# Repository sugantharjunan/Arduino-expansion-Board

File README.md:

# Arduino UNO Sensor Shield PCB

An **Arduino UNO Compatible Sensor Shield** designed using **KiCad 10**. This PCB expands the Arduino UNO by providing dedicated Digital, Analog, Power, and Ground headers while integrating useful onboard components such as a buzzer, potentiometer, LEDs, and push buttons for rapid prototyping and embedded system development.

---

# Features

- Arduino UNO Compatible
- Digital I/O Expansion Headers
- Analog Input Headers
- Dedicated 5V & GND Headers
- On-board Buzzer
- 10K Potentiometer
- Power Indicator LED
- Two User LEDs
- Two Push Buttons
- Easy Sensor Connections
- Compact 2-Layer PCB
- Designed in KiCad 10

---

# Hardware Components

| Component | Quantity |
|-----------|---------:|
| Female Header 2.54mm | Multiple |
| Piezo Buzzer | 1 |
| 10K Potentiometer | 1 |
| Push Button | 2 |
| LEDs | 3 |
| 220Ω Resistors | 3 |
| Arduino UNO Header Set | 1 |

---

# PCB Specifications

| Parameter | Value |
|-----------|-------|
| PCB Software | KiCad 10 |
| PCB Layers | 2 |
| Board Type | Arduino UNO Shield |
| Header Pitch | 2.54 mm |
| Mounting Holes | 4 |
| PCB Color | Green |

---

# Pin Configuration

## Digital Pins

- D0 – D13
- PWM Support
- Dedicated 5V Header
- Dedicated GND Header

## Analog Pins

- A0 – A5

---

# Onboard Components

## 🔔 Buzzer

Provides audible feedback for alarms, notifications, and debugging.

---

## 🎛 Potentiometer

- 5V
- GND
- Analog Output

Useful for testing analog inputs and ADC applications.

---

## 💡 Power LED

Indicates that the board is powered.

---

## 💡 User LEDs

- LED connected to D2
- LED connected to D3

Useful for testing digital outputs.

---

## 🔘 Push Buttons

Two onboard push buttons connected for digital input testing.

---

# Applications

- Arduino Learning
- Sensor Interfacing
- Embedded System Development
- IoT Prototyping
- Robotics
- College Mini Projects
- Rapid Hardware Testing

---

# Folder Structure

```
Arduino-UNO-Sensor-Shield/
│
├── PCB/
│   ├── Arduino_UNO_Shield.kicad_pcb
│   ├── Arduino_UNO_Shield.kicad_sch
│
├── Gerber/
│
├── BOM/
│
├── Images/
│   ├── Top_3D.png
│   ├── Bottom_3D.png
│   ├── PCB_Layout.png
│   └── Schematic.png
│
├── README.md
│
└── LICENSE
```

---

# Software Used

- KiCad 10
- Git
- GitHub

---

# Future Improvements

- I2C Connector
- SPI Header
- Servo Headers
- OLED Interface
- Relay Output
- ESP32 Compatibility
- External Power Connector

---

# Author

**Suganth Arjunan**

📧 Email: your-email@example.com

🔗 GitHub: https://github.com/SuganthArjunan

💼 LinkedIn: https://www.linkedin.com/in/suganth-arjunan

🌐 Portfolio: https://sugantharjunan.github.io/SuganthArjunan-portfolio/

---

# License

This project is licensed under the MIT License.

---

⭐ **If you found this project useful, please give it a Star on GitHub!**

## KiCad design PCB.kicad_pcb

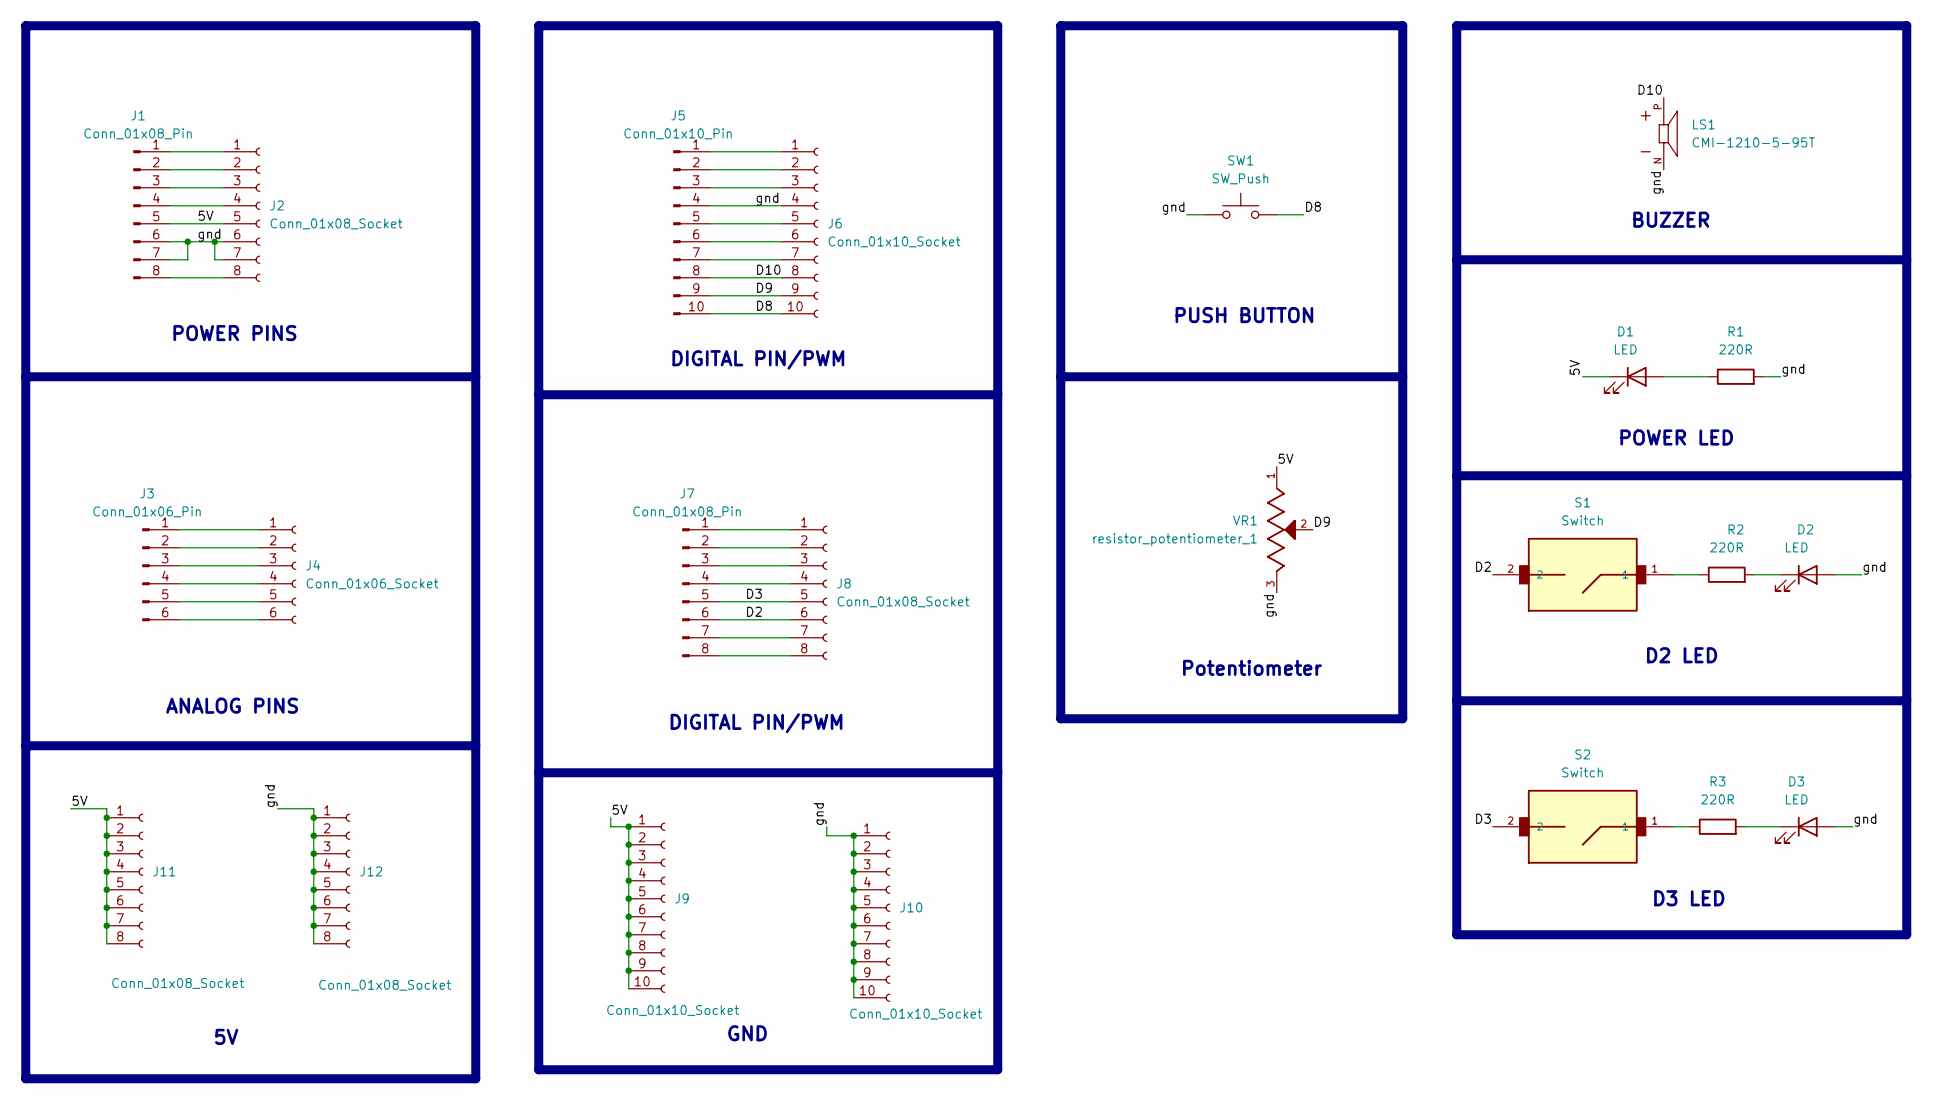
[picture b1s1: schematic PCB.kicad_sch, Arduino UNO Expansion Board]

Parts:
D1, D2, D3: LED; LED_0805_2012Metric
J1, J7: Conn_01x08_Pin; PinHeader_1x08_P2.54mm_Vertical
J2, J8, J11, J12: Conn_01x08_Socket; PinSocket_1x08_P2.54mm_Vertical
J3: Conn_01x06_Pin; PinHeader_1x06_P2.54mm_Vertical
J4: Conn_01x06_Socket; PinSocket_1x06_P2.54mm_Vertical
J5: Conn_01x10_Pin; PinHeader_1x10_P2.54mm_Vertical
J6, J9, J10: Conn_01x10_Socket; PinSocket_1x10_P2.54mm_Vertical
LS1: CMI-1210-5-95T; XDCR_CMI-1210-5-95T; PARTREV 1.0
R1, R2, R3: 220R; R_0805_2012Metric
S1, S2: Switch
SW1: SW_Push; SW_Push_1P1T_NO_CK_KSC7xxJ
VR1: resistor_potentiometer_1; TRIM_3296W-OT1-103; PARTREV 05/16

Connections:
/5V: D1.1 (K), J1.5, J2.5, J9.1, J9.2, J9.3, J9.4, J9.5, J9.6, J9.7, J9.8, J9.9, J9.10, J11.1, J11.2, J11.3, J11.4, J11.5, J11.6, J11.7, J11.8, VR1.1
/D2: J7.6, J8.6, S1.2
/D3: J7.5, J8.5, S2.2
/D8: J5.10, J6.10, SW1.2
/D9: J5.9, J6.9, VR1.2
/D10: J5.8, J6.8, LS1.P
/gnd: D2.2 (A), D3.2 (A), J1.6, J1.7, J2.6, J2.7, J5.4, J6.4, J10.1, J10.2, J10.3, J10.4, J10.5, J10.6, J10.7, J10.8, J10.9, J10.10, J12.1, J12.2, J12.3, J12.4, J12.5, J12.6, J12.7, J12.8, LS1.N, R1.2, SW1.1, VR1.3
unnamed: D1.2 (A), R1.1
unnamed: D2.1 (K), R2.2
unnamed: D3.1 (K), R3.2
unnamed: J1.1, J2.1
unnamed: J1.2, J2.2
unnamed: J1.3, J2.3
unnamed: J1.4, J2.4
unnamed: J1.8, J2.8
unnamed: J3.1, J4.1
unnamed: J3.2, J4.2
unnamed: J3.3, J4.3
unnamed: J3.4, J4.4
unnamed: J3.5, J4.5
unnamed: J3.6, J4.6
unnamed: J5.1, J6.1
unnamed: J5.2, J6.2
unnamed: J5.3, J6.3
unnamed: J5.5, J6.5
unnamed: J5.6, J6.6
unnamed: J5.7, J6.7
unnamed: J7.1, J8.1
unnamed: J7.2, J8.2
unnamed: J7.3, J8.3
unnamed: J7.4, J8.4
unnamed: J7.7, J8.7
unnamed: J7.8, J8.8
unnamed: R2.1, S1.1
unnamed: R3.1, S2.1

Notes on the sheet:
BUZZER
ANALOG PINS
D3 LED
DIGITAL PIN/PWM
D2 LED
Potentiometer
POWER PINS
POWER LED
GND
PUSH BUTTON

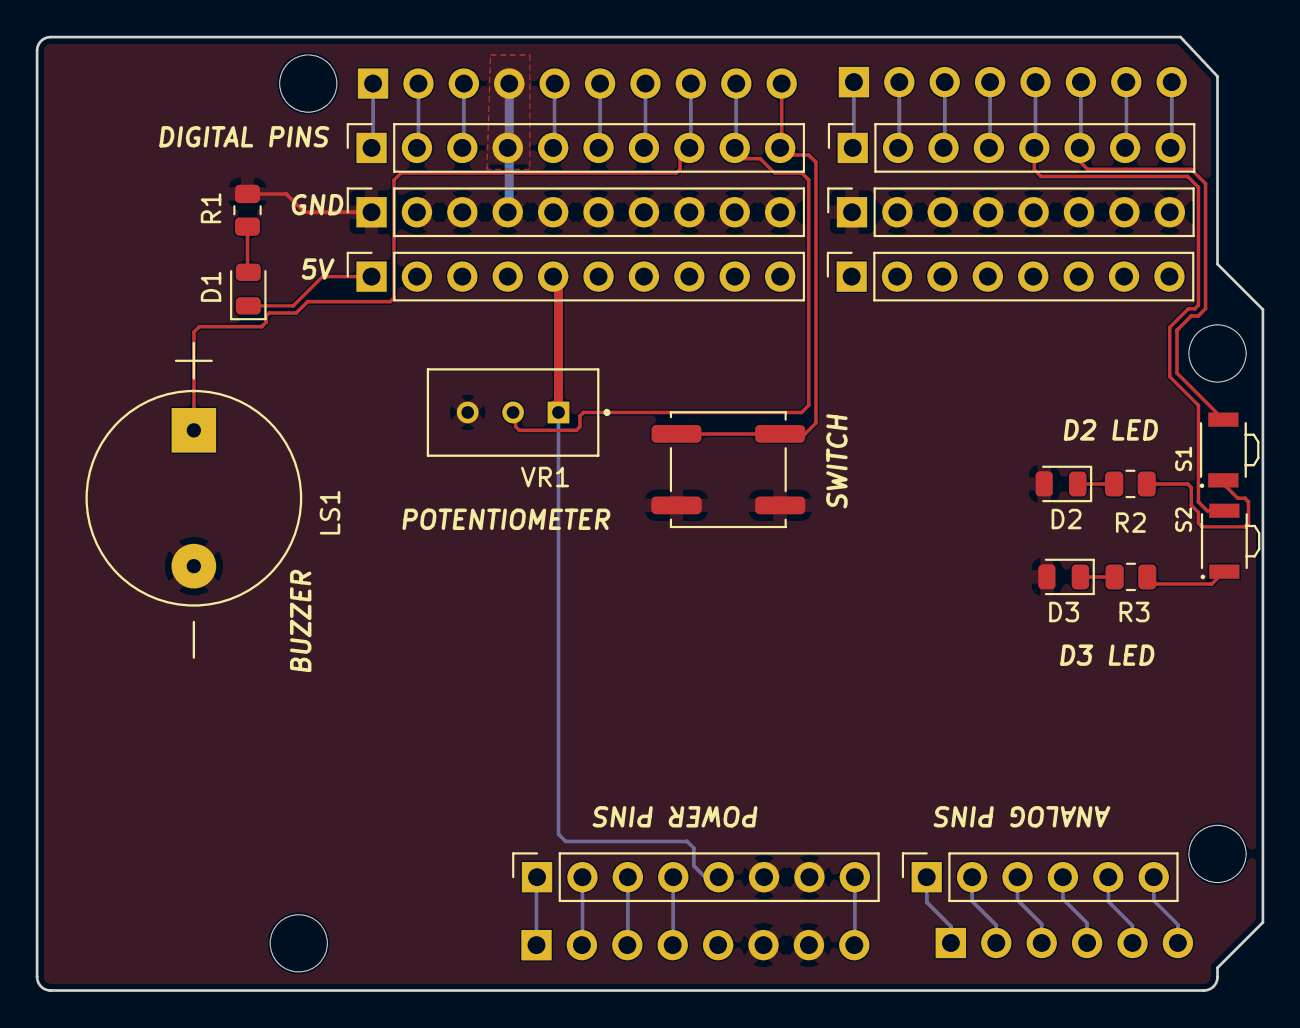
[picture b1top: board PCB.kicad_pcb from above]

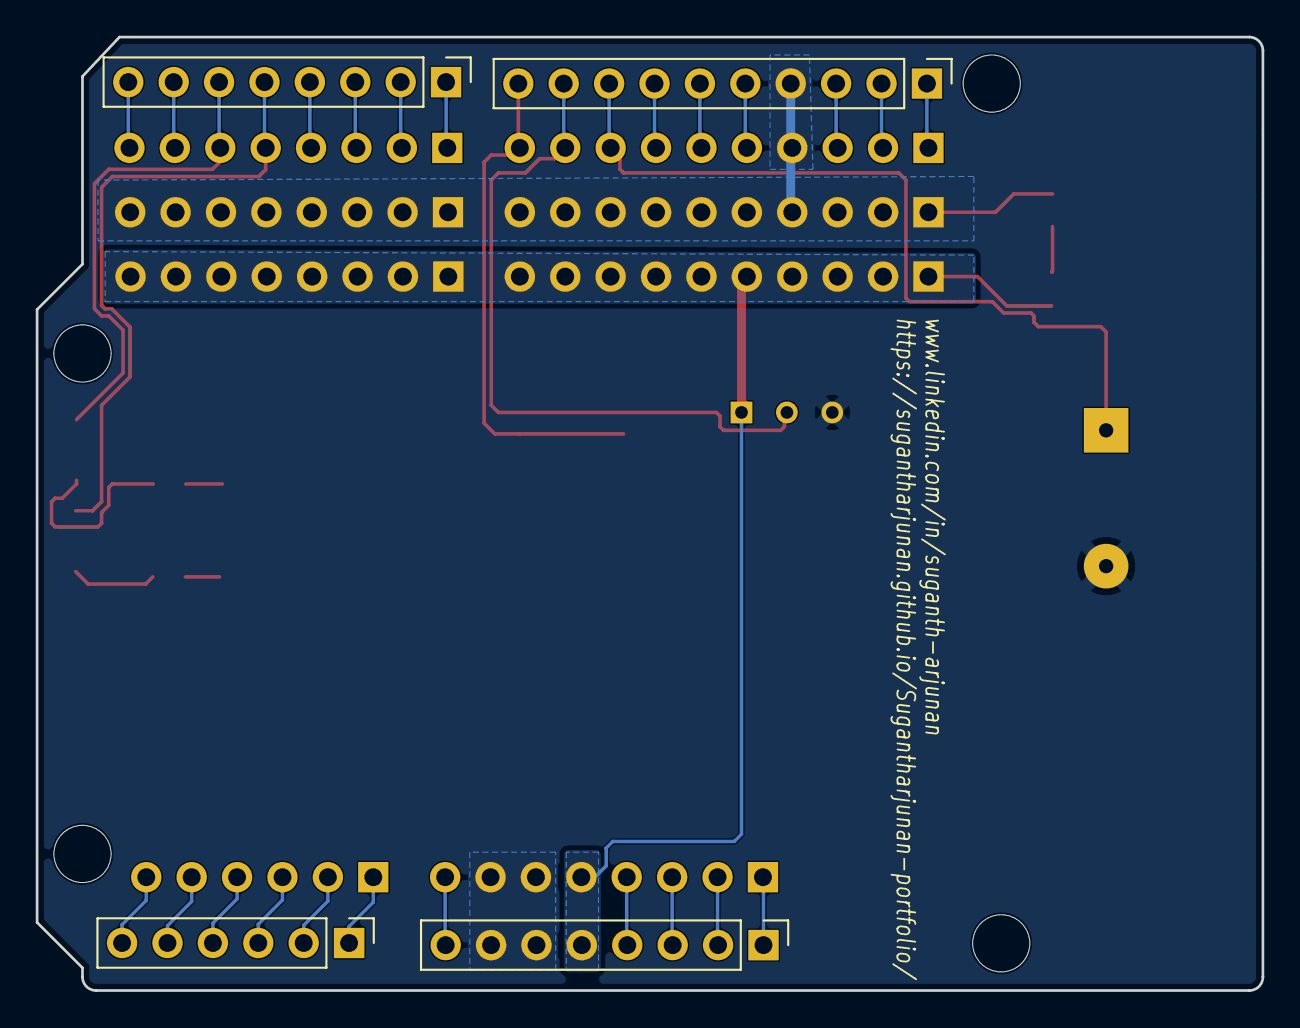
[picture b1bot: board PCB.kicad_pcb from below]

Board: 2 copper layers, 68.6 x 53.3 mm, 23 parts (4 on the bottom side), 35 nets.

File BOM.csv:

"Id;""Designator"";""Footprint"";""Quantity"";""Designation"";""Supplier and ref"";",,,
"1;""", , ," "";"""";4;"""";;;"
"2;""D1", D2," D3"";""LED_0805_2012Metric"";3;""LED"";;;",
"3;""J1"," J7"";""PinHeader_1x08_P2.54mm_Vertical"";2;""Conn_01x08_Pin"";;;",,
"4;""J2", J8, J11," J12"";""PinSocket_1x08_P2.54mm_Vertical"";4;""Conn_01x08_Socket"";;;"
"5;""J3"";""PinHeader_1x06_P2.54mm_Vertical"";1;""Conn_01x06_Pin"";;;",,,
"6;""J4"";""PinSocket_1x06_P2.54mm_Vertical"";1;""Conn_01x06_Socket"";;;",,,
"7;""J5"";""PinHeader_1x10_P2.54mm_Vertical"";1;""Conn_01x10_Pin"";;;",,,
"8;""J6", J9," J10"";""PinSocket_1x10_P2.54mm_Vertical"";3;""Conn_01x10_Socket"";;;",
"9;""LS1"";""XDCR_CMI-1210-5-95T"";1;""CMI-1210-5-95T"";;;",,,
"10;""R1", R2," R3"";""R_0805_2012Metric"";3;""220R"";;;",
"11;""S1"," S2"";""Switch"";2;""Switch"";;;",,
"12;""SW1"";""SW_Push_1P1T_NO_CK_KSC7xxJ"";1;""SW_Push"";;;",,,
"13;""VR1"";""TRIM_3296W-OT1-103"";1;""resistor_potentiometer_1"";;;",,,
